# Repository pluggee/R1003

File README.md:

# R1003
Analog/Digital I/O (Analog/Digital)
License
-------
R1003 is released under the GNU GPL v3, which you can find at <http://www.gnu.org/licenses/gpl-3.0.en.html>,
Check License.md for more details.

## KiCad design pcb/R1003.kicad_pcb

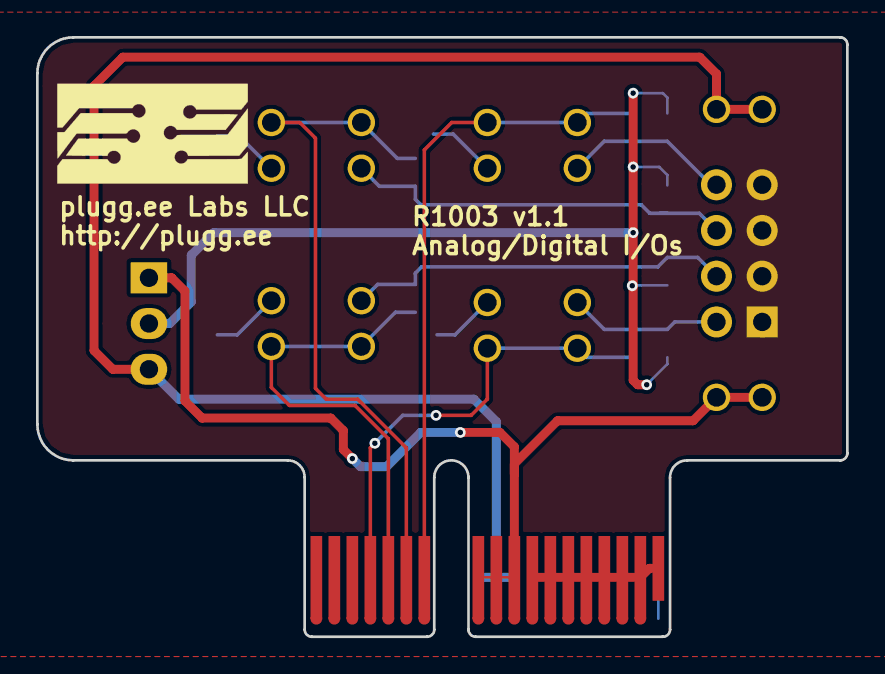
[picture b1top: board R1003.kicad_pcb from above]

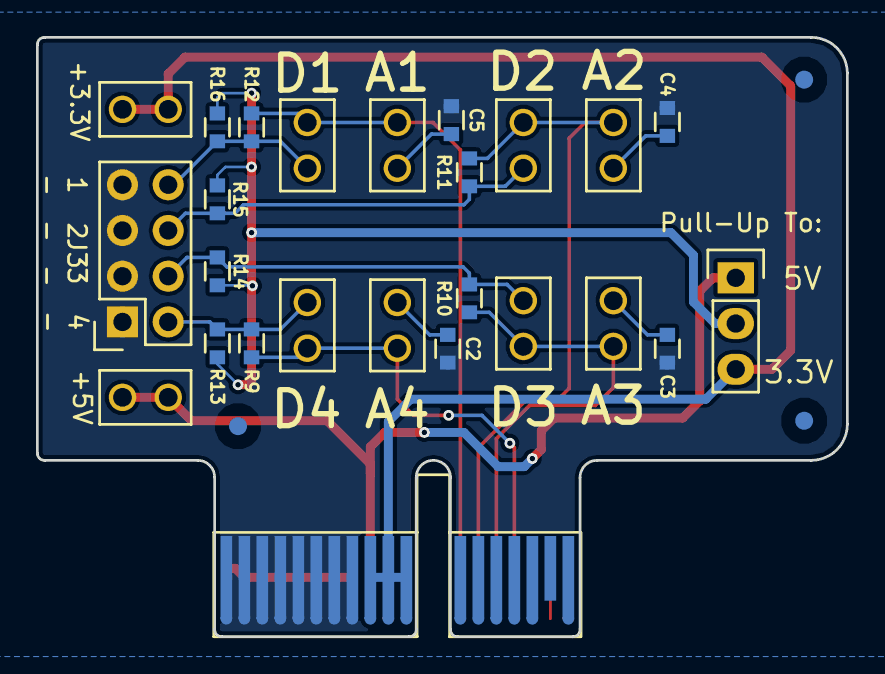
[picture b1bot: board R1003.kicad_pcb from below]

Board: 2 copper layers, 45.0 x 33.3 mm, 29 parts (28 on the bottom side), 17 nets.

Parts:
A1: ART; pluggeeLabsIcon-11x6
C2, C3, C4, C5: CC0603KRX7R9BB104; CAPC0603
FID1, FID2, FID3: FIDTOP001
J1: PCIEXPRESS-X1
J2: CONN_01X03; CONN254P-01X03
J3: CONN254P-02X04
J4, J5, J6, J7, J8, J9, J10, J11, J12, J13: SOCKET254P-01X02; SOCKET254P-01X02_2
R9, R10, R11, R12: RC0603FR-0710KL; RESC0603
R13, R14, R15, R16: RC0603FR-074K7L; RESC0603

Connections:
+3V3: J1.B9, J1.B10, J1.B11, J2.3, J4.1, J4.2
+5V: J1.A9, J1.A10, J1.A11, J2.1, J13.1, J13.2
/CX1: C5.1, J8.1
/CX2: C4.1, J7.1
/CX3: C3.1, J6.1
/CX4: C2.1, J5.1
/X1: J3.8, J11.1, R12.1, R16.2
/X2: J3.6, J10.1, R11.1, R15.2
/X3: J3.4, J9.1, R10.1, R14.2
/X4: J3.2, J12.1, R9.1, R13.2
GND: C2.2, C3.2, C4.2, C5.2, J1.B1, J1.B2, J1.B3, J1.B4, J1.B5, J1.B6, J1.B7, J1.B8, J3.1, J3.3, J3.5, J3.7
HT: J1.A1, J1.A2, J1.A3, J1.A4, J1.A5, J1.A6, J1.A7, J1.A8
PX1: J1.A12, J8.2, J11.2, R12.2
PX2: J1.A13, J7.2, J10.2, R11.2
PX3: J1.A14, J6.2, J9.2, R10.2
PX4: J1.A15, J5.2, J12.2, R9.2
P_JUMP: J2.2, R13.1, R14.1, R15.1, R16.1

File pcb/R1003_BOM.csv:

sep=;
Reference; Value; Footprint; Datasheet; Manufacturer; MPN; SKU; Res; Tol; Pwr; C; Vmax; Type
J1;PCIEXPRESS-X1;Main:PCIEXPRESS-X1;;Amphenol FCI;10018784-10200TLF;;;;;;;
J2;CONN_01X03;Main:SOCKET254P-01X03;;Amphenol FCI;68001-403HLF;STUFF;;;;;;
J3;CONN254P-02X04;Main:CONN254P-02X04;;Amphenol FCI;68021-408HLF;STUFF;;;;;;
R14;RC0603FR-074K7L;Main:RESC0603;;Yageo;RC0603FR-074K7L;STUFF;4.7 kΩ;±1%;100 mW;;;
R10;RC0603FR-0710KL;Main:RESC0603;;Yageo;RC0603FR-0710KL;STUFF;10.0 kΩ;±1%;100 mW;;;
C3;CC0603KRX7R9BB104;Main:CAPC0603;;Yageo;CC0603KRX7R9BB104;STUFF;;±10%;;100 nF;50.0V;X7R
R13;RC0603FR-074K7L;Main:RESC0603;;Yageo;RC0603FR-074K7L;STUFF;4.7 kΩ;±1%;100 mW;;;
R9;RC0603FR-0710KL;Main:RESC0603;;Yageo;RC0603FR-0710KL;STUFF;10.0 kΩ;±1%;100 mW;;;
C2;CC0603KRX7R9BB104;Main:CAPC0603;;Yageo;CC0603KRX7R9BB104;STUFF;;±10%;;100 nF;50.0V;X7R
J12;SOCKET254P-01X02;Main:SOCKET254P-01X02_2;;Amphenol FCI;861400021YO1LF;STUFF;;;;;;
R15;RC0603FR-074K7L;Main:RESC0603;;Yageo;RC0603FR-074K7L;STUFF;4.7 kΩ;±1%;100 mW;;;
R11;RC0603FR-0710KL;Main:RESC0603;;Yageo;RC0603FR-0710KL;STUFF;10.0 kΩ;±1%;100 mW;;;
C4;CC0603KRX7R9BB104;Main:CAPC0603;;Yageo;CC0603KRX7R9BB104;STUFF;;±10%;;100 nF;50.0V;X7R
R16;RC0603FR-074K7L;Main:RESC0603;;Yageo;RC0603FR-074K7L;STUFF;4.7 kΩ;±1%;100 mW;;;
R12;RC0603FR-0710KL;Main:RESC0603;;Yageo;RC0603FR-0710KL;STUFF;10.0 kΩ;±1%;100 mW;;;
C5;CC0603KRX7R9BB104;Main:CAPC0603;;Yageo;CC0603KRX7R9BB104;STUFF;;±10%;;100 nF;50.0V;X7R
A1;ART;pluggee:pluggeeLabsIcon-11x6;
J5;SOCKET254P-01X02;Main:SOCKET254P-01X02_2;;Amphenol FCI;861400021YO1LF;STUFF;;;;;;
J9;SOCKET254P-01X02;Main:SOCKET254P-01X02_2;;Amphenol FCI;861400021YO1LF;STUFF;;;;;;
J10;SOCKET254P-01X02;Main:SOCKET254P-01X02_2;;Amphenol FCI;861400021YO1LF;STUFF;;;;;;
J11;SOCKET254P-01X02;Main:SOCKET254P-01X02_2;;Amphenol FCI;861400021YO1LF;STUFF;;;;;;
J6;SOCKET254P-01X02;Main:SOCKET254P-01X02_2;;Amphenol FCI;861400021YO1LF;STUFF;;;;;;
J7;SOCKET254P-01X02;Main:SOCKET254P-01X02_2;;Amphenol FCI;861400021YO1LF;STUFF;;;;;;
J8;SOCKET254P-01X02;Main:SOCKET254P-01X02_2;;Amphenol FCI;861400021YO1LF;STUFF;;;;;;
J13;SOCKET254P-01X02;Main:SOCKET254P-01X02_2;;Amphenol FCI;861400021YO1LF;NOSTUFF;;;;;;
J4;SOCKET254P-01X02;Main:SOCKET254P-01X02_2;;Amphenol FCI;861400021YO1LF;NOSTUFF;;;;;;
FID1;FIDTOP001;Main:FIDTOP001;
FID3;FIDTOP001;Main:FIDTOP001;
FID2;FIDTOP001;Main:FIDTOP001;

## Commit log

2016-07-30 completed layout
2016-07-30 added gerbers
2016-08-19 added BOM
2017-02-02 added license
2017-03-28 getting ready for release
2017-03-28 added fiducials
2017-03-29 finalized BOM and added position assembly files
2017-04-16 fixed silk screen version
2017-04-27 updated BOM with headers with proper height
